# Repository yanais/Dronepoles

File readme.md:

circuito.io
===========

* Circuito.io is a system for generating a circuit schematic & accompanying code samples.
Circuito.io generate the schematic & code based on your selection of micro-controller, i/o and power devices.

The circuito.io team is composed of Matan Harel, Eyal Mehoudar, Barak Yemini, Uri Ramot, Dor Tal, Pavel Tarnopolsky, Ofer Berman and Yana Segalis.

* For more information, see the website at: http://circuito.io
You can also like circuito.io on Facebook at: https://www.facebook.com/circuito.io

* for any question on the code or layout, please don't hesitate to contact us at hello@circuito.io.

How to read this repository
---------------------------
You are here because you ised circuito.io and asked for a circuit and code sample for your project.
This is your project folder, you'll find here:
* bom.txt - all the parts used in designing the circuit - your chosen parts & any additionals that may be required for the circuit to work.
* firmware folder - includes all code need to operate the i/o devices using the micro-controller. firmware.ino is the main logic file.
* PCB folder - where you'll find the schematic diagram and breadboards view as a Fritzing file, and as two png files.

License
-------

To the extent possible under law, [Circuito.io](http://circuito.io) has waived all copyright and related or neighbouring rights to this work.

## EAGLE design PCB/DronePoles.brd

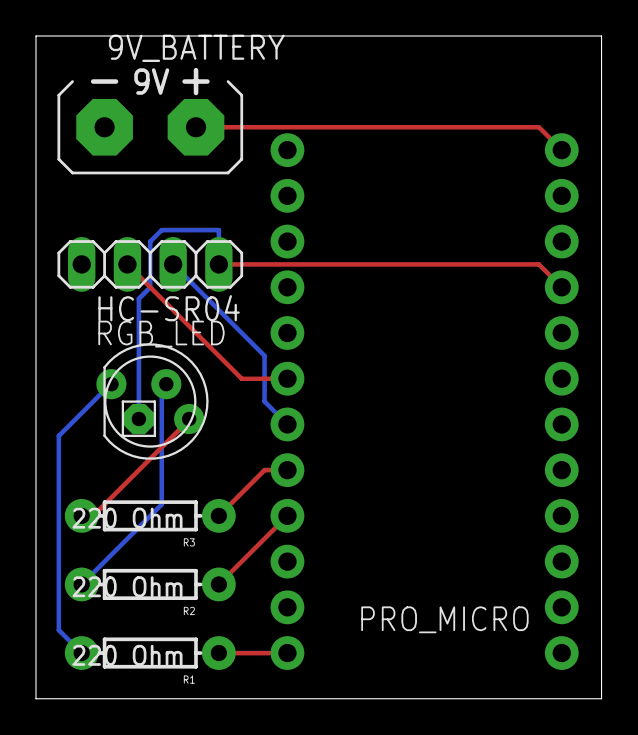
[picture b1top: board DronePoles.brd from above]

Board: 2 copper layers, 31.4 x 36.8 mm, 7 parts (0 on the bottom side), 11 nets.

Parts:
9V_BATTERY: AB9V
HC-SR04: Ultrasonic sensor; 1X04
PRO_MICRO: ARDUINO_PRO_MICRO
R1, R2, R3: 220 Ohm; AXIAL-0.3
RGB_LED: RGBLED_CA; LED5MMRGB

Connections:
9V: 9V_BATTERY.+, PRO_MICRO.24
ECHO: HC-SR04.3, PRO_MICRO.6
GND: 9V_BATTERY.-, HC-SR04.4, PRO_MICRO.3
unnamed: R3.P$2, RGB_LED.4
unnamed: R2.P$2, RGB_LED.3
unnamed: R1.P$2, RGB_LED.1
unnamed: PRO_MICRO.9, R2.P$1
unnamed: PRO_MICRO.12, R1.P$1
unnamed: PRO_MICRO.8, R3.P$1
TRIG: HC-SR04.2, PRO_MICRO.7
VCC: HC-SR04.1, PRO_MICRO.21, RGB_LED.2

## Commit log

2015-12-15 init
2015-12-16 Circiuto version 1
2015-12-16 with firmware
2015-12-16 schmatics picture added
2015-12-22 Fritzing files, code not done yet
2015-12-23 singleton pattern
2015-12-27 New HCSR04 version, works well
2015-12-27 BOM added
2015-12-27 BOM updated
2015-12-27 BOM updated, YML style
2015-12-27 readme added

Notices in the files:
readme.md:
[CC0](http://creativecommons.org/publicdomain/zero/1.0/)
parts and their libraries:
SparkFun-Boards: Licensing: Creative Commons ShareAlike 4.0 International - https://creativecommons.org/licenses/by-sa/4.0
